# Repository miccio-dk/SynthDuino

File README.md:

# SynthDuino

Arduino-based drum machine and master keyboard, with MIDI support and sound synthesis.

Developed as part of my Italian technical high school (Istituto Tecnico Industriale Statale) final project.

[Entry on official Arduino Forum](http://forum.arduino.cc/index.php?topic=104901.0)

## Installation

1. Print the PCBs (a breadboard will do too)
2. Upload the code
3. Assemble everything
4. Play!

## Usage

TODO: Write usage instructions

## Contributing

1. Fork it!
2. Create your feature branch: `git checkout -b my-new-feature`
3. Commit your changes: `git commit -am 'Add some feature'`
4. Push to the branch: `git push origin my-new-feature`
5. Submit a pull request :D

## History

- 19/02 menu handling
- 20/02 bugfix
- 26/02 settings configuration
- 03/03 object-oriented twist: begin migration
- 17/03 migration complete
- 18/03 new libraries: settings, synthesis e pads
- 19/03 multiplexer handling
- 23/03 waveform generation algorithm

## License

Code released under the terms of GPL v3 or higher.

Other documentation licensed under Creative Commons (BY-NC-ND v3).

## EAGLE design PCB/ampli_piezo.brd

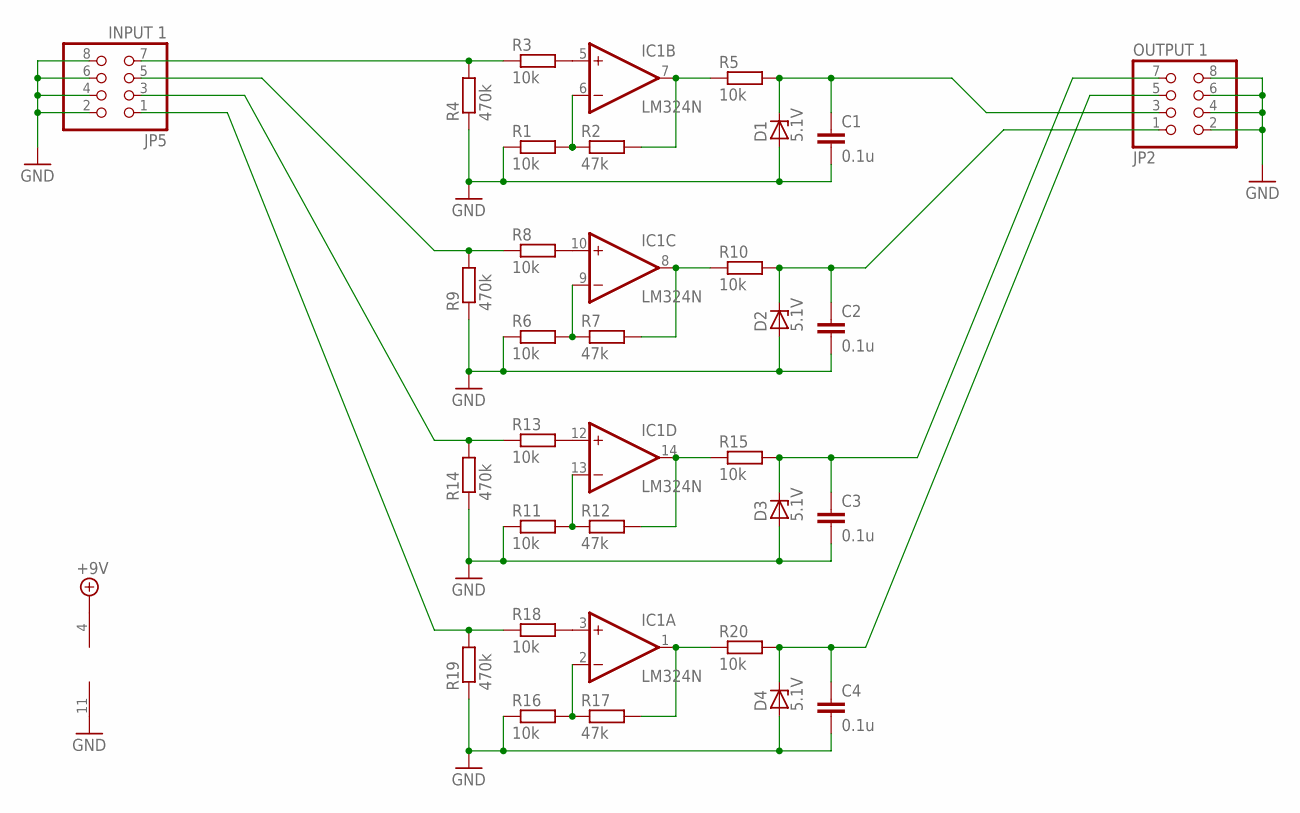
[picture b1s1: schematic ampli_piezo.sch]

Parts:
C1, C2, C3, C4: 0.1u; C050-025X075
D1, D2, D3, D4: 5.1V; DO35Z10
IC1: LM324N; DIL14
JP2: OUTPUT 1; 2X04/90
JP5: INPUT 1; 2X04/90
R1, R3, R5, R6, R8, R10, R11, R13, R15, R16, R18, R20: 10k; 0207/10
R2, R7, R12, R17: 47k; 0207/10
R4, R9, R14, R19: 470k; 0207/10

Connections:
+9V: IC1.4 (V+)
GND: C1.2, C2.2, C3.2, C4.2, D1.A, D2.A, D3.A, D4.A, IC1.11 (V-), JP2.2, JP2.4, JP2.6, JP2.8, JP5.2, JP5.4, JP5.6, JP5.8, R1.1, R4.1, R6.1, R9.1, R11.1, R14.1, R16.1, R19.1
unnamed: IC1.12 (+IN), R13.2
unnamed: IC1.10 (+IN), R8.2
unnamed: IC1.5 (+IN), R3.2
unnamed: IC1.3 (+IN), R18.2
unnamed: IC1.6 (-IN), R1.2, R2.1
unnamed: IC1.14 (OUT), R12.2, R15.1
unnamed: IC1.1 (OUT), R17.2, R20.1
unnamed: IC1.7 (OUT), R2.2, R5.1
unnamed: JP5.7, R3.1, R4.2
unnamed: C1.1, D1.C, JP2.3, R5.2
unnamed: IC1.9 (-IN), R6.2, R7.1
unnamed: IC1.8 (OUT), R7.2, R10.1
unnamed: JP5.5, R8.1, R9.2
unnamed: C2.1, D2.C, JP2.1, R10.2
unnamed: IC1.13 (-IN), R11.2, R12.1
unnamed: JP5.3, R13.1, R14.2
unnamed: C3.1, D3.C, JP2.7, R15.2
unnamed: IC1.2 (-IN), R16.2, R17.1
unnamed: JP5.1, R18.1, R19.2
unnamed: C4.1, D4.C, JP2.5, R20.2

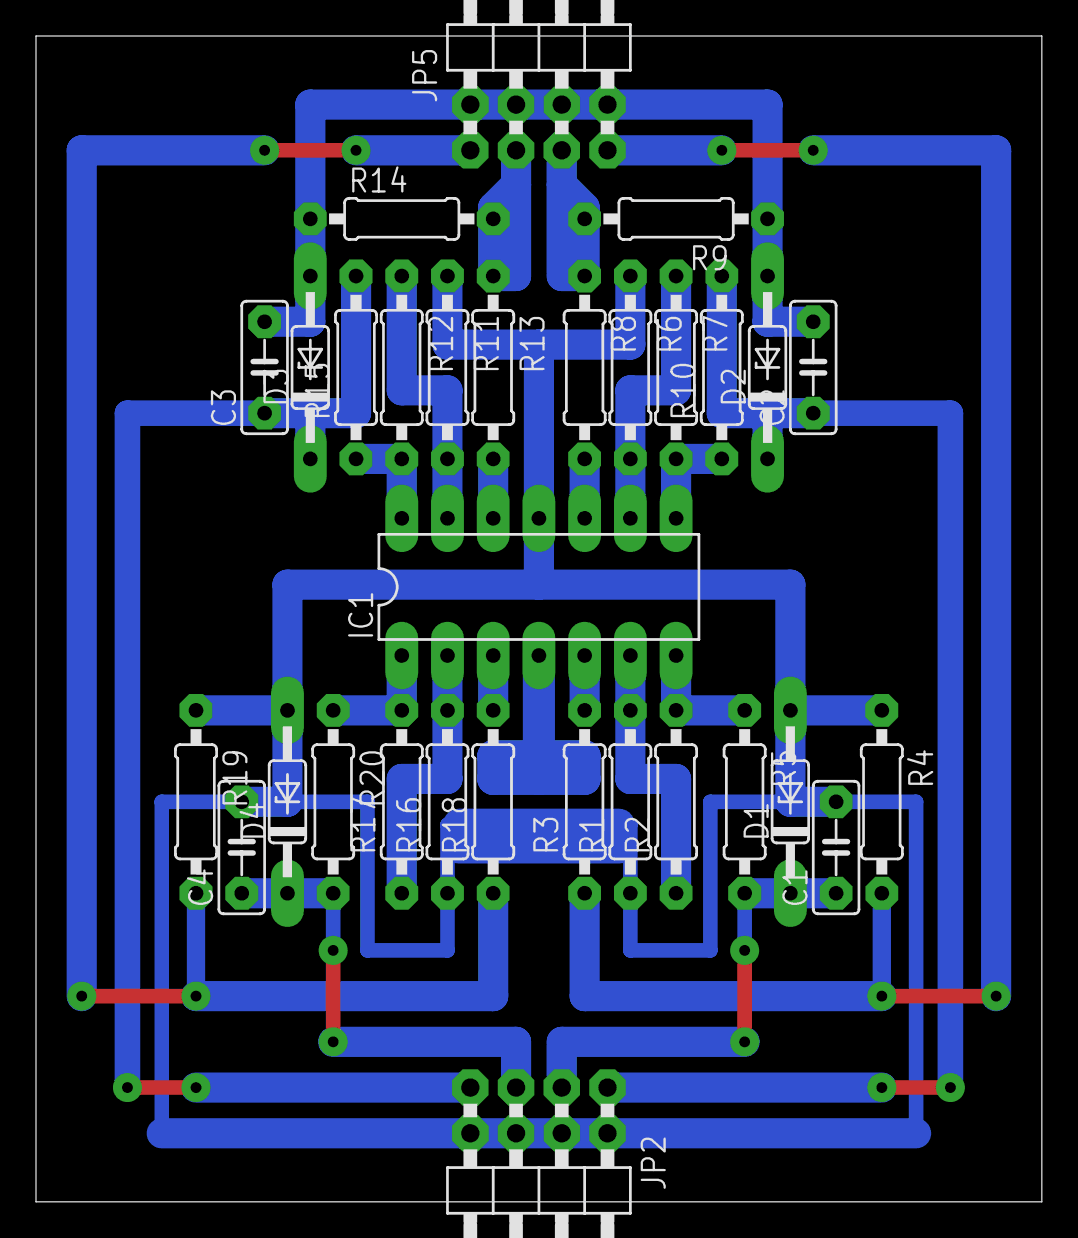
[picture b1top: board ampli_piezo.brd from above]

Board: 2 copper layers, 55.9 x 64.8 mm, 31 parts (0 on the bottom side), 21 nets.

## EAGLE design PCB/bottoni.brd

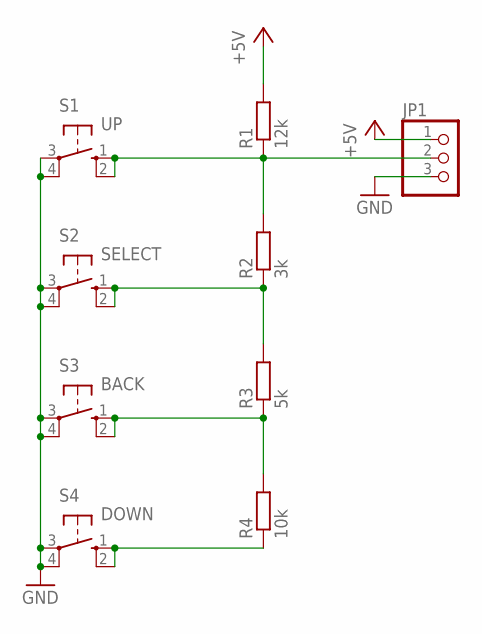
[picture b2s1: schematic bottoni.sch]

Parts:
JP1: PINHD-1X3/90; 1X03/90
R1: 12k; 0207/10
R2: 3k; 0207/10
R3: 5k; 0207/10
R4: 10k; 0207/10
S1: UP; B3F-10XX
S2: SELECT; B3F-10XX
S3: BACK; B3F-10XX
S4: DOWN; B3F-10XX

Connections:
+5V: JP1.1, R1.2
GND: JP1.3, S1.3, S1.4 (P1), S2.3, S2.4 (P1), S3.3, S3.4 (P1), S4.3, S4.4 (P1)
unnamed: JP1.2, R1.1, R2.2, S1.1 (S), S1.2 (S1)
unnamed: R2.1, R3.2, S2.1 (S), S2.2 (S1)
unnamed: R3.1, R4.2, S3.1 (S), S3.2 (S1)
unnamed: R4.1, S4.1 (S), S4.2 (S1)

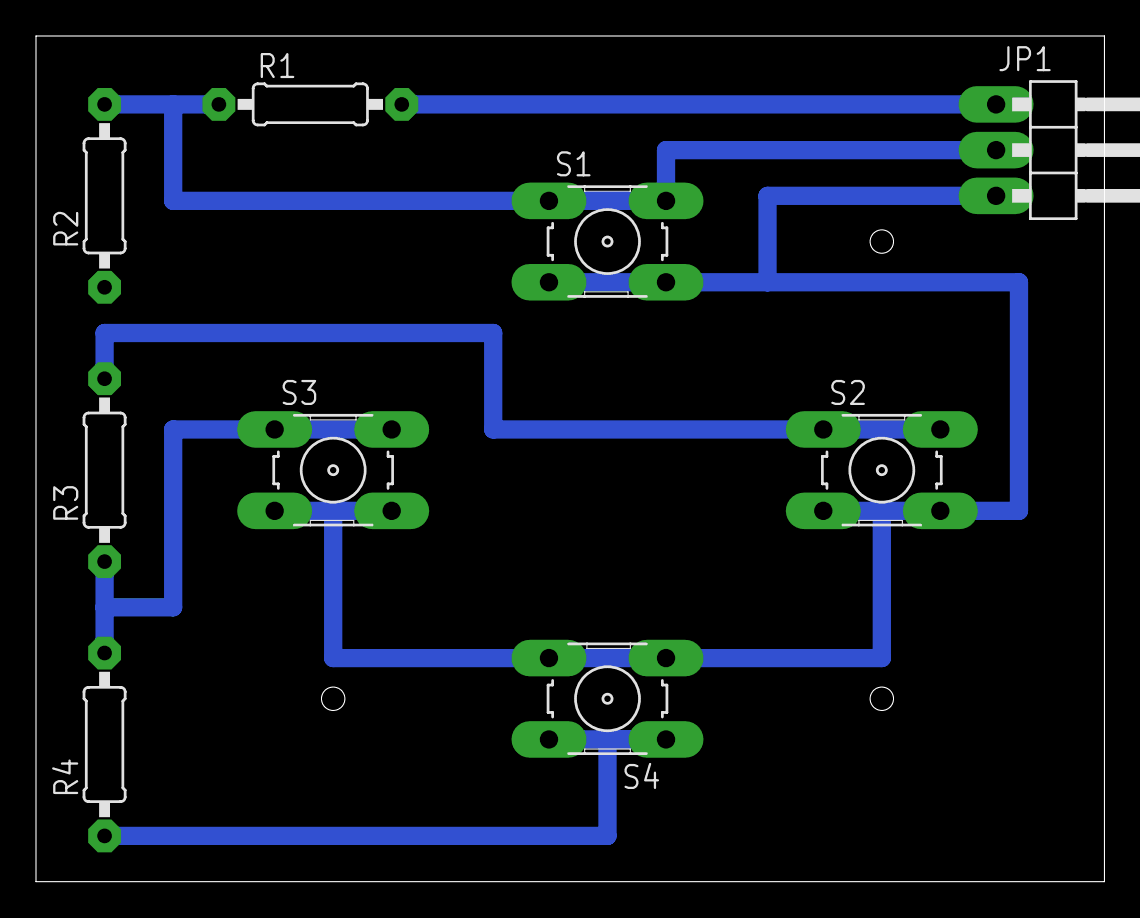
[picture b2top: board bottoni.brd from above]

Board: 2 copper layers, 59.4 x 47.0 mm, 9 parts (0 on the bottom side), 6 nets.

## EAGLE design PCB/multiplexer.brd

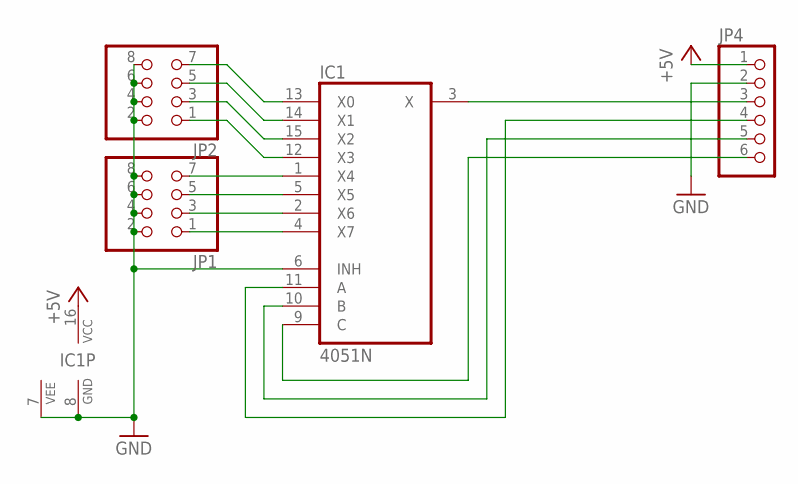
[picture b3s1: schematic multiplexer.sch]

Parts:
IC1: 4051N; DIL16
JP1, JP2: PINHD-2X4/90; 2X04/90
JP4: PINHD-1X6/90; 1X06/90

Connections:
+5V: IC1.16 (VCC), JP4.1
GND: IC1.6 (INH), IC1.7 (VEE), IC1.8 (GND), JP1.2, JP1.4, JP1.6, JP1.8, JP2.2, JP2.4, JP2.6, JP2.8, JP4.2
unnamed: IC1.4 (X7), JP1.1
unnamed: IC1.2 (X6), JP1.3
unnamed: IC1.5 (X5), JP1.5
unnamed: IC1.1 (X4), JP1.7
unnamed: IC1.12 (X3), JP2.1
unnamed: IC1.15 (X2), JP2.3
unnamed: IC1.14 (X1), JP2.5
unnamed: IC1.13 (X0), JP2.7
unnamed: IC1.3 (X), JP4.3
unnamed: IC1.9 (C), JP4.6
unnamed: IC1.10 (B), JP4.5
unnamed: IC1.11 (A), JP4.4

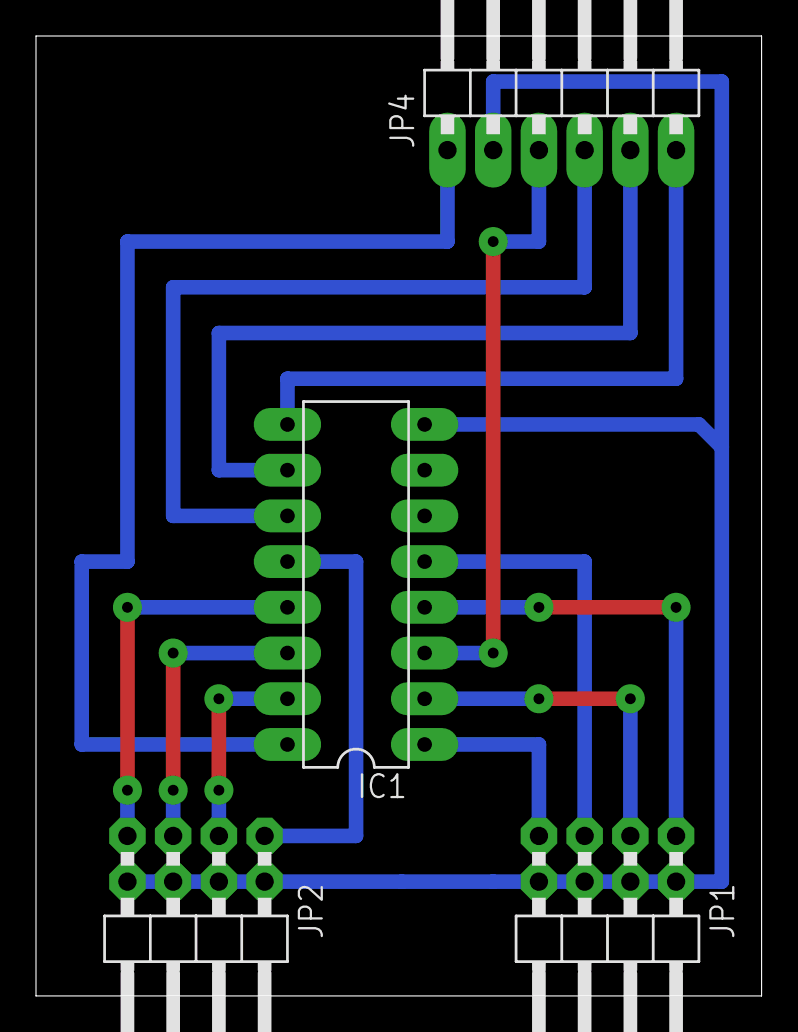
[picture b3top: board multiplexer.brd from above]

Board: 2 copper layers, 40.3 x 53.3 mm, 4 parts (0 on the bottom side), 14 nets.

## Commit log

2015-02-28 Add LICENSE file via addalicense.com
2015-02-28 project files
2015-03-30 final version
    found latest version of the project, updated all files
